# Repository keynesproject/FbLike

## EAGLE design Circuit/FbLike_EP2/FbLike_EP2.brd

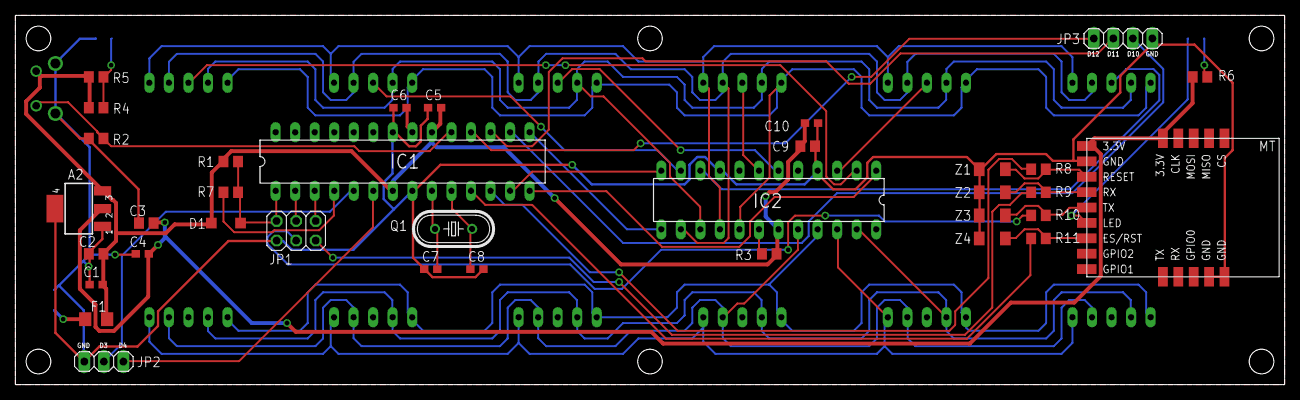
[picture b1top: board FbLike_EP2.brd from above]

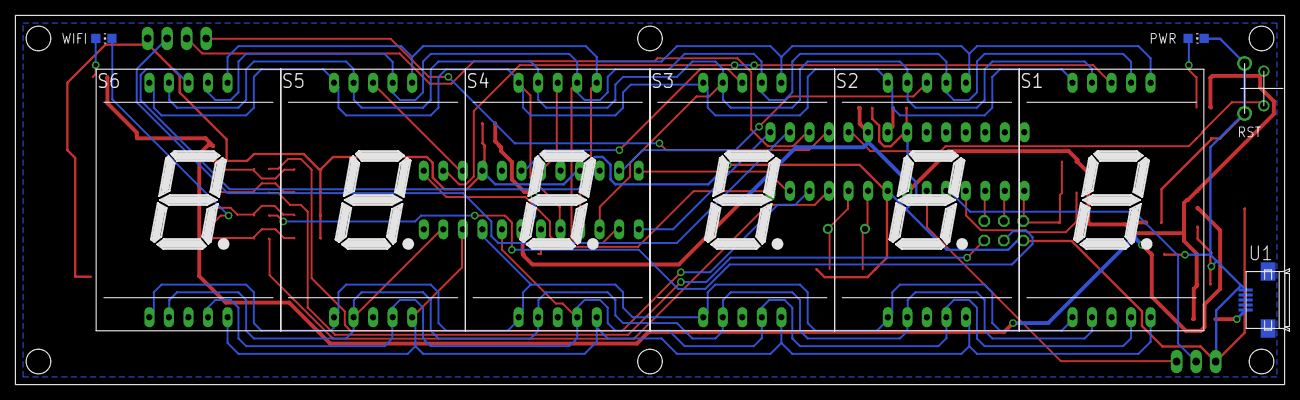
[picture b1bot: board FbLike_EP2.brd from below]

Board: 2 copper layers, 165.0 x 48.0 mm, 45 parts (10 on the bottom side), 46 nets.

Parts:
A2: 3.3V; SOT223
C1, C4, C5, C6, C10: 0.1uf; C0603
C2, C3, C9: 10uf; C0805
C7, C8: 22pf; C0603
D1: 1N4148; SOD123
F1: 0.5A; R1206
IC1: DIL28-3
IC2: DIL24-3
JP1: 2X03
JP2: 1X03
JP3: 1X04
MT: HLK-M35-PAD
PWR: RED; CHIP-LED0805
Q1: 16Mhz; HC49U-V
R1, R2: 10K; R0805
R3: 22.6K; R0805
R4, R5, R6, R7: 1K; R0805
R8, R9, R10, R11: 200; R0805
RST: BUTTON-66-90DEG; BUTTON-6*6-90DEG
S1, S2, S3, S4, S5, S6: 7SEG-1INCH
U1: MICRO-USB-B
WIFI: BLUE; CHIP-LED0805
Z1, Z2, Z3, Z4: 3.3V; LL-34

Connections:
+3V3: A2.2, C3.1, C4.1, MT.P$1, MT.P$19, R6.1
+5V: A2.3, C1.1, C2.1, C5.1, C9.1, C10.1, D1.C, F1.2, IC1.7, IC1.20, IC2.19, R1.1, R3.2, R4.2, R5.1, RST.P$3
BTN_RST: IC1.19, R2.2, RST.P$2
GND: A2.1, A2.4, C1.2, C2.2, C3.2, C4.2, C5.2, C6.1, C7.1, C8.1, C9.2, C10.2, IC1.8, IC1.22, IC2.4, IC2.9, JP1.1, JP2.1, JP3.4, MT.P$2, MT.P$13, MT.P$14, PWR.C, R2.1, RST.P$1, RST.P$4, U1.P5, Z1.2, Z2.2, Z3.2, Z4.2
IC1_RESET: IC1.4, R7.2
IC2_CLK: IC1.15, IC2.13
IC2_DIN: IC1.14, IC2.1
IC2_LOAD: IC1.13, IC2.12
JP1_P2: D1.A, IC1.1, JP1.2, R1.2, R7.1
JP1_P4: IC1.2, JP1.4
JP1_P6: IC1.3, JP1.6
JP2_P2: IC1.5, JP2.2
JP2_P3: IC1.6, JP2.3
JP3_P1: IC1.18, JP3.1
JP3_P2: IC1.17, JP3.2
JP3_P3: IC1.16, JP3.3
M35_ES: IC1.11, R11.1
M35_RESET: IC1.12, R8.1
unnamed: R6.2, WIFI.A
unnamed: C6.2, IC1.21
unnamed: C7.2, IC1.9, Q1.2
unnamed: C8.2, IC1.10, Q1.1
unnamed: IC2.14, S1.7, S2.7, S3.7, S4.7, S5.7, S6.7
unnamed: IC2.16, S1.6, S2.6, S3.6, S4.6, S5.6, S6.6
unnamed: IC2.20, S1.4, S2.4, S3.4, S4.4, S5.4, S6.4
unnamed: IC2.23, S1.2, S2.2, S3.2, S4.2, S5.2, S6.2
unnamed: IC2.21, S1.1, S2.1, S3.1, S4.1, S5.1, S6.1
unnamed: IC2.10, S6.8
unnamed: IC2.15, S1.9, S2.9, S3.9, S4.9, S5.9, S6.9
unnamed: IC2.17, S1.10, S2.10, S3.10, S4.10, S5.10, S6.10
unnamed: IC2.22, S1.5, S2.5, S3.5, S4.5, S5.5, S6.5
unnamed: IC2.3, S5.8
unnamed: IC2.7, S4.8
unnamed: IC2.6, S3.8
unnamed: IC2.11, S2.8
unnamed: IC2.2, S1.8
unnamed: JP1.5, R9.1
unnamed: JP1.3, R10.1
unnamed: MT.P$3, R8.2, Z1.1
unnamed: IC2.18, R3.1
unnamed: MT.P$4, R9.2, Z2.1
unnamed: MT.P$5, R10.2, Z3.1
unnamed: MT.P$7, R11.2, Z4.1
unnamed: PWR.A, R4.1, R5.2
WIFI_LED: MT.P$6, WIFI.C
XUSB: F1.1, U1.P1

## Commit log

2015-06-29 New Project
2015-10-17 Add New Project Use new wifi modular MT7681
2015-10-19 bug fix : The data from Facebook api request analyze function.
2015-12-06 Add animation
2015-12-06 Modify Pin Table
2015-12-06 Add Unit test folder
2015-12-06 Add Fblike Ep2 circuit
2015-12-07 增加錯誤顯示 WIFI沒連線到AP -> IF E03 FB請求的ID錯誤 -> Fb EId
2015-12-07 數值微調
2015-12-15 新增 數字遞增滾動特效
2015-12-19 增加 數字特效
2015-12-19 加入 Watchdog 功能
2016-01-22 修正顯示動畫
2016-09-17 Backup
